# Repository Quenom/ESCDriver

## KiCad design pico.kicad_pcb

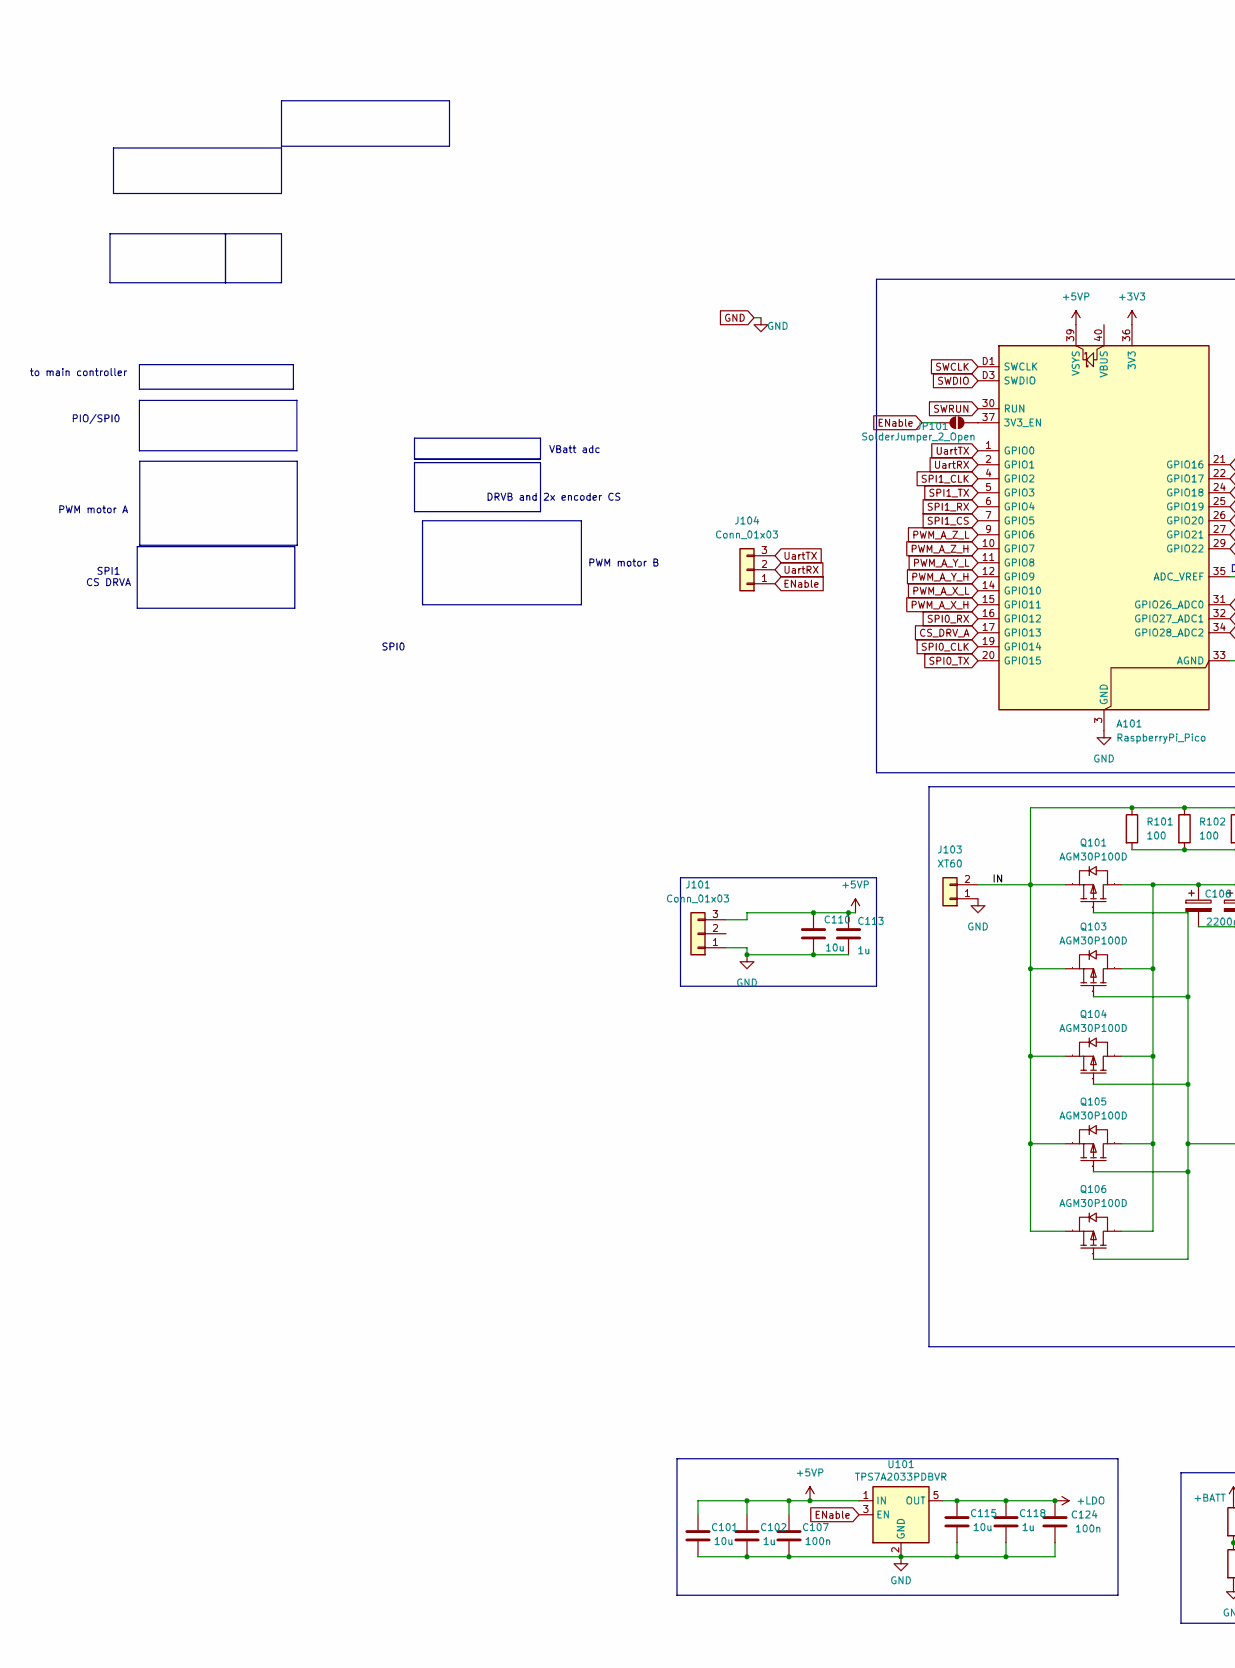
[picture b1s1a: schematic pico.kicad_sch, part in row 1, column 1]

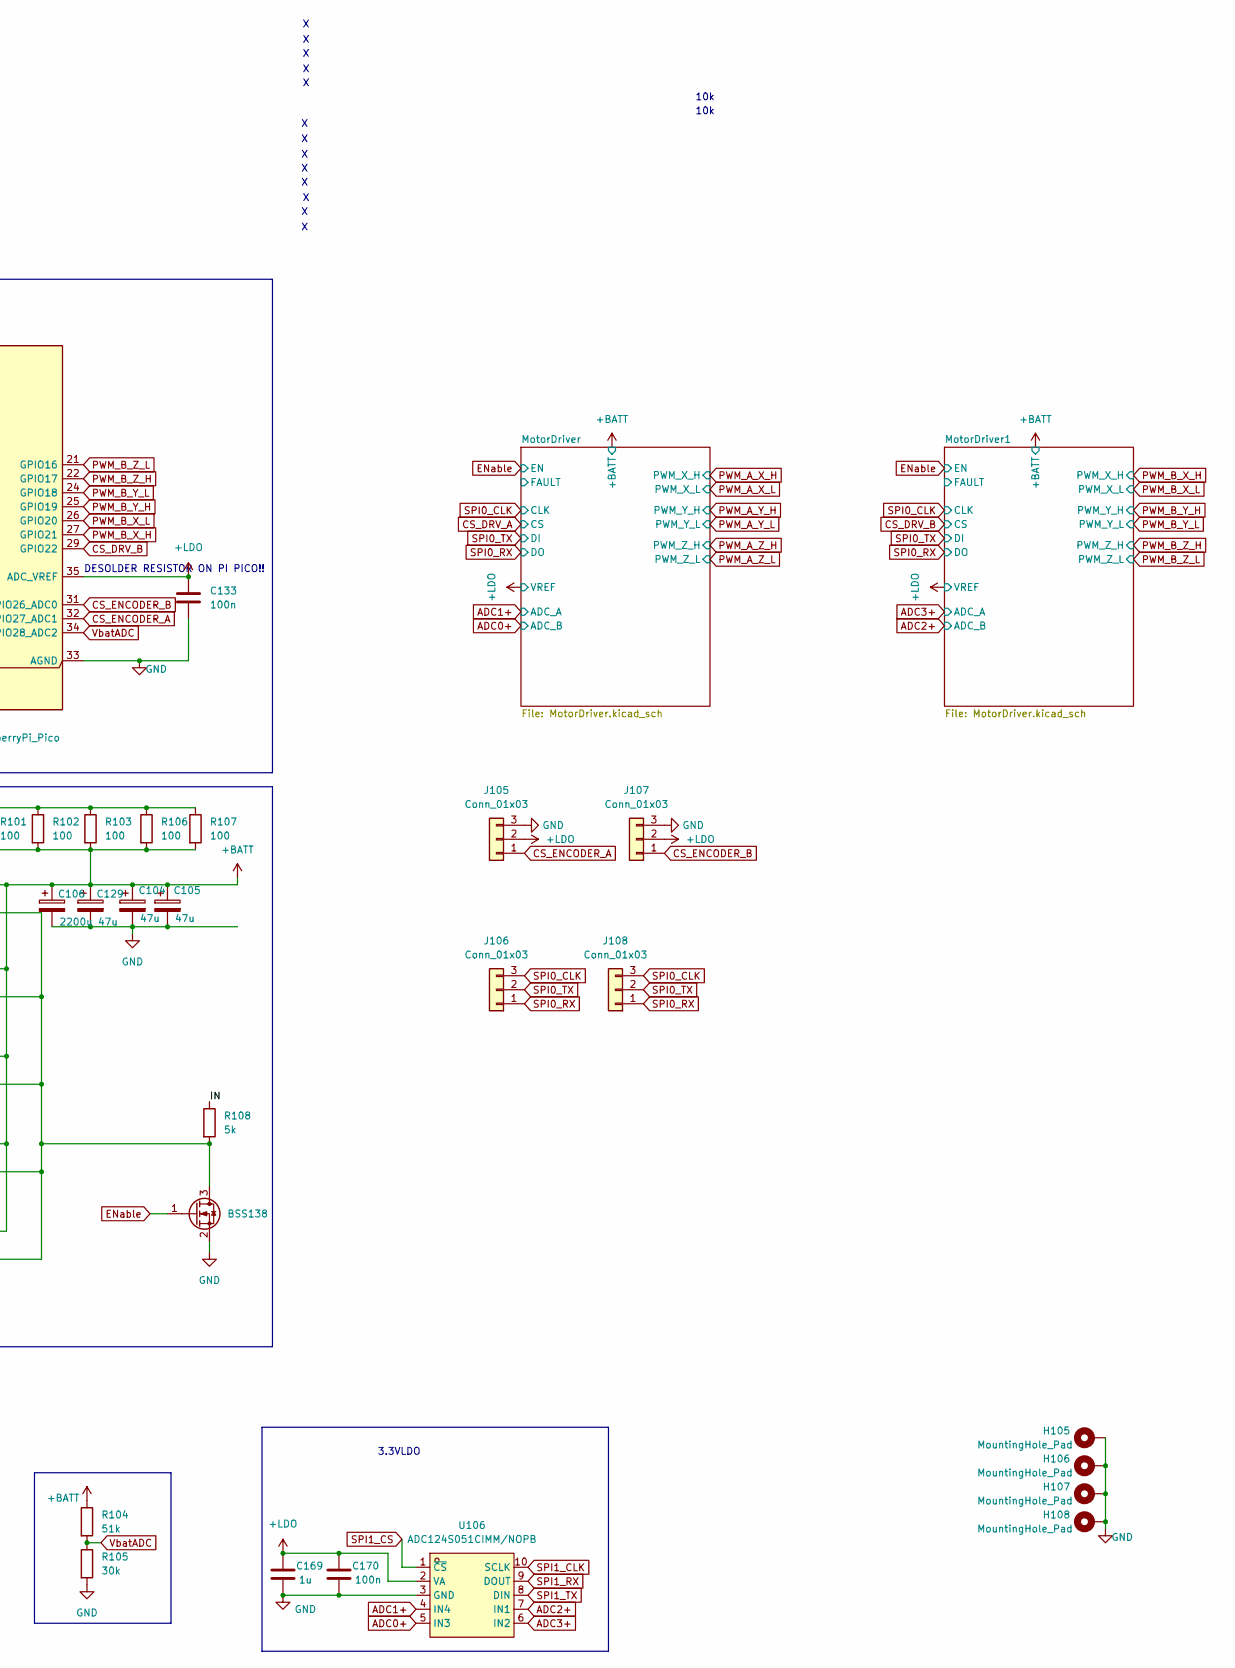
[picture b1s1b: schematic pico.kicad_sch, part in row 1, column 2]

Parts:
A101: RaspberryPi_Pico; RaspberryPi_Pico_SMD_HandSolder
C101, C110, C115: 10u; 1206_Resistor
C102, C113, C118, C169: 1u; 1206_Resistor
C104, C105, C129: 47u; CP_Radial_D6.3mm_P2.50mm
C106: 2200u; CP_Radial_D18.0mm_P7.50mm
C107, C124, C133, C170: 100n; 1206_Resistor
H105, H106, H107, H108: MountingHole_Pad; MountingHole_3.2mm_M3_Pad_Via
J101, J104, J105, J106, J107, J108: Conn_01x03; JST_XH_B3B-XH-A_1x03_P2.50mm_Vertical
J103: XT60; AMASS_XT60PW-M_1x02_P7.20mm_Horizontal
JP101: SolderJumper_2_Open; SolderJumper-2_P1.3mm_Open_RoundedPad1.0x1.5mm
Q101, Q103, Q104, Q105, Q106: AGM30P100D; TO-252-3_L6.6-W6.1-P4.57-LS9.9-BR-CW; Manufacturer Part AGM30P100D; LCSC Part Name 1个P沟道 耐压:30V 电流:128A
Q102: BSS138; SOT-23
R101, R102, R103, R106, R107: 100; 1206_Resistor
R104: 51k; 1206_Resistor
R105: 30k; 1206_Resistor
R108: 5k; 1206_Resistor
U101: TPS7A2033PDBVR; SOT-23-5
U106: ADC124S051CIMM/NOPB; VSSOP-10_L3.0-W3.0-P0.50-LS4.9-BL; Supply Voltage 2.7V~5.25V; LCSC Part C2651323

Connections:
+3V3: A101.36 (3V3)
+5VP: A101.39 (VSYS), C101.1, C102.1, C107.1, C110.1, C113.1, J101.3, U101.1 (IN)
+BATT: C104.1, C105.1, C106.1, C129.1, Q101.2 (D), Q103.2 (D), Q104.2 (D), Q105.2 (D), Q106.2 (D), R101.2, R102.2, R103.2, R104.1, R106.2, R107.2; also elsewhere on the board
+LDO: A101.35 (ADC_VREF), C115.1, C118.1, C124.1, C133.1, C169.1, C170.1, J105.2, J107.2, U101.5 (OUT), U106.2 (VA); also elsewhere on the board
/IN: J103.2, Q101.3 (S), Q103.3 (S), Q104.3 (S), Q105.3 (S), Q106.3 (S), R101.1, R102.1, R103.1, R106.1, R107.1, R108.1
ADC0+: U106.5 (IN3); also elsewhere on the board
ADC1+: U106.4 (IN4); also elsewhere on the board
ADC2+: U106.7 (IN1); also elsewhere on the board
ADC3+: U106.6 (IN2); also elsewhere on the board
CS_DRV_A: A101.17 (GPIO13); also elsewhere on the board
CS_DRV_B: A101.29 (GPIO22); also elsewhere on the board
CS_ENCODER_A: A101.32 (GPIO27_ADC1), J105.1
CS_ENCODER_B: A101.31 (GPIO26_ADC0), J107.1
ENable: J104.1, JP101.1 (A), Q102.1 (G), U101.3 (EN); also elsewhere on the board
GND: A101.3 (GND), A101.8 (GND), A101.13 (GND), A101.18 (GND), A101.23 (GND), A101.28 (GND), A101.33 (AGND), A101.38 (GND), A101.D2 (GND), C101.2, C102.2, C104.2, C105.2, C106.2, C107.2, C110.2, C113.2, C115.2, C118.2, C124.2, C129.2, C133.2, C169.2, C170.2, H105.1, H106.1, H107.1, H108.1, J101.1, J103.1, J105.3, J107.3, Q102.2 (S), R105.2, U101.2 (GND), U106.3 (GND); also elsewhere on the board
unnamed: A101.37 (3V3_EN), JP101.2 (B)
unnamed: Q101.1 (G), Q102.3 (D), Q103.1 (G), Q104.1 (G), Q105.1 (G), Q106.1 (G), R108.2
PWM_A_X_H: A101.15 (GPIO11); also elsewhere on the board
PWM_A_X_L: A101.14 (GPIO10); also elsewhere on the board
PWM_A_Y_H: A101.12 (GPIO9); also elsewhere on the board
PWM_A_Y_L: A101.11 (GPIO8); also elsewhere on the board
PWM_A_Z_H: A101.10 (GPIO7); also elsewhere on the board
PWM_A_Z_L: A101.9 (GPIO6); also elsewhere on the board
PWM_B_X_H: A101.27 (GPIO21); also elsewhere on the board
PWM_B_X_L: A101.26 (GPIO20); also elsewhere on the board
PWM_B_Y_H: A101.25 (GPIO19); also elsewhere on the board
PWM_B_Y_L: A101.24 (GPIO18); also elsewhere on the board
PWM_B_Z_H: A101.22 (GPIO17); also elsewhere on the board
PWM_B_Z_L: A101.21 (GPIO16); also elsewhere on the board
SPI0_CLK: A101.19 (GPIO14), J106.3, J108.3; also elsewhere on the board
SPI0_RX: A101.16 (GPIO12), J106.1, J108.1; also elsewhere on the board
SPI0_TX: A101.20 (GPIO15), J106.2, J108.2; also elsewhere on the board
SPI1_CLK: A101.4 (GPIO2), U106.10 (SCLK)
SPI1_CS: A101.7 (GPIO5), U106.1 (~CS)
SPI1_RX: A101.6 (GPIO4), U106.9 (DOUT)
SPI1_TX: A101.5 (GPIO3), U106.8 (DIN)
SWCLK: A101.D1 (SWCLK)
SWDIO: A101.D3 (SWDIO)
SWRUN: A101.30 (RUN)
UartRX: A101.2 (GPIO1), J104.2
UartTX: A101.1 (GPIO0), J104.3
VbatADC: A101.34 (GPIO28_ADC2), R104.2, R105.1

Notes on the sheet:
3.3VLDO
PIO/SPI0
DRVB and 2x encoder CS
SPI0
DESOLDER RESISTOR ON PI PICO!!
PWM motor A
VBatt adc
PWM motor B
SPI1 CS DRVA
10k
to main controller

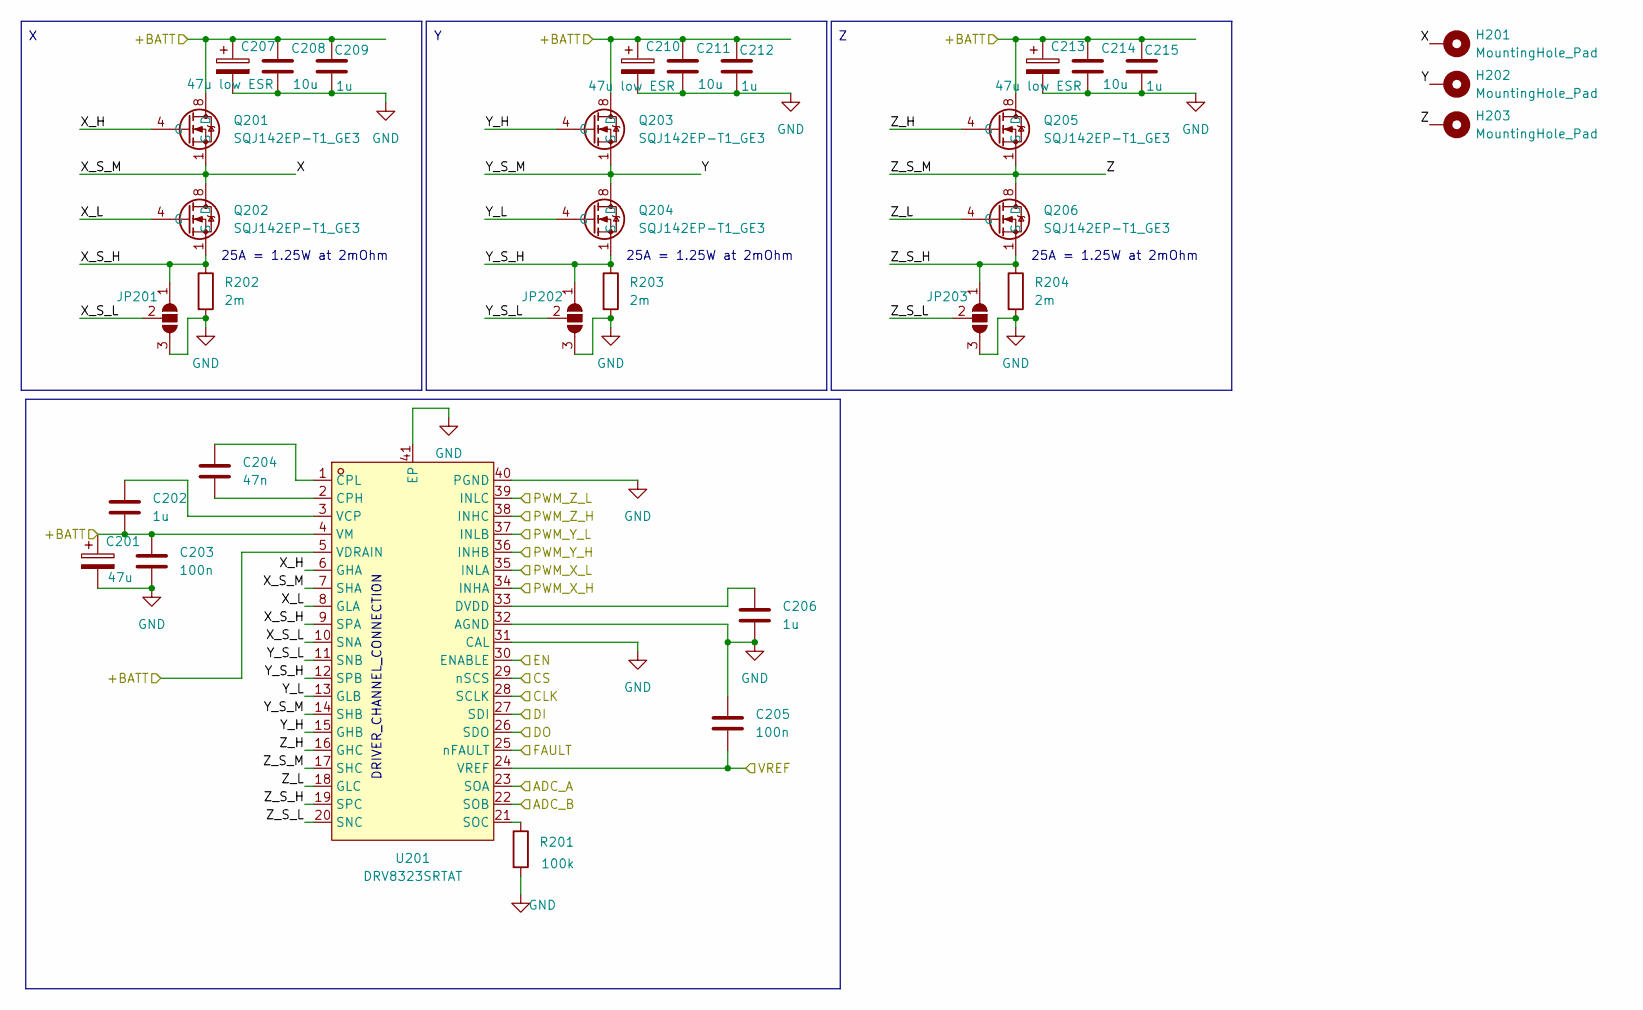
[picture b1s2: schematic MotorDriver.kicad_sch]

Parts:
C201: 47u; CP_Radial_D6.3mm_P2.50mm
C202, C206, C209, C212, C215: 1u; 1206_Resistor
C203, C205: 100n; 1206_Resistor
C204: 47n; 1206_Resistor
C207, C210, C213: 47u low ESR; CP_Radial_D6.3mm_P2.50mm
C208, C211, C214: 10u; 1206_Resistor
H201, H202, H203: MountingHole_Pad; SolderWire-2sqmm_1x01_D2mm_OD3.9mm
JP201, JP202, JP203: SolderJumper_3_Open; SolderJumper-3_P1.3mm_Open_RoundedPad1.0x1.5mm_NumberLabels
Q201, Q202, Q203, Q204, Q205, Q206: SQJ142EP-T1_GE3; POWERPAK-SO-8_L5.9-W4.9-P1.27-BL; LCSC Part C5758799
R201: 100k; 1206_Resistor
R202, R203, R204: 2m; R_2512_6332Metric_Pad1.40x3.35mm_HandSolder
U201: DRV8323SRTAT; WQFN-40_L6.0-W6.0-P0.50-TL-EP4.5; Supply Voltage 6V~60V; LCSC Part C2150452

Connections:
+BATT: C201.1, C202.2, C203.1, C207.1, C208.1, C209.1, C210.1, C211.1, C212.1, C213.1, C214.1, C215.1, Q201.8 (D), Q203.8 (D), Q205.8 (D), U201.4 (VM), U201.5 (VDRAIN); also elsewhere on the board
+LDO: C205.2, U201.24 (VREF); also elsewhere on the board
/MotorDriver/FAULT: U201.25 (nFAULT)
/MotorDriver/X: H201.1, Q201.1 (S), Q202.8 (D), U201.7 (SHA)
/MotorDriver/X_H: Q201.4 (G), U201.6 (GHA)
/MotorDriver/X_L: Q202.4 (G), U201.8 (GLA)
/MotorDriver/X_S_H: JP201.1 (A), Q202.1 (S), R202.1, U201.9 (SPA)
/MotorDriver/X_S_L: JP201.2 (C), U201.10 (SNA)
/MotorDriver/Y: H202.1, Q203.1 (S), Q204.8 (D), U201.14 (SHB)
/MotorDriver/Y_H: Q203.4 (G), U201.15 (GHB)
/MotorDriver/Y_L: Q204.4 (G), U201.13 (GLB)
/MotorDriver/Y_S_H: JP202.1 (A), Q204.1 (S), R203.1, U201.12 (SPB)
/MotorDriver/Y_S_L: JP202.2 (C), U201.11 (SNB)
/MotorDriver/Z: H203.1, Q205.1 (S), Q206.8 (D), U201.17 (SHC)
/MotorDriver/Z_H: Q205.4 (G), U201.16 (GHC)
/MotorDriver/Z_L: Q206.4 (G), U201.18 (GLC)
/MotorDriver/Z_S_H: JP203.1 (A), Q206.1 (S), R204.1, U201.19 (SPC)
/MotorDriver/Z_S_L: JP203.2 (C), U201.20 (SNC)
ADC0+: U201.22 (SOB); also elsewhere on the board
ADC1+: U201.23 (SOA); also elsewhere on the board
CS_DRV_A: U201.29 (nSCS); also elsewhere on the board
ENable: U201.30 (ENABLE); also elsewhere on the board
GND: C201.2, C203.2, C205.1, C206.2, C207.2, C208.2, C209.2, C210.2, C211.2, C212.2, C213.2, C214.2, C215.2, JP201.3 (B), JP202.3 (B), JP203.3 (B), R201.2, R202.2, R203.2, R204.2, U201.31 (CAL), U201.32 (AGND), U201.40 (PGND), U201.41 (EP); also elsewhere on the board
unnamed: C204.2, U201.2 (CPH)
unnamed: C204.1, U201.1 (CPL)
unnamed: C206.1, U201.33 (DVDD)
unnamed: R201.1, U201.21 (SOC)
unnamed: C202.1, U201.3 (VCP)
PWM_A_X_H: U201.34 (INHA); also elsewhere on the board
PWM_A_X_L: U201.35 (INLA); also elsewhere on the board
PWM_A_Y_H: U201.36 (INHB); also elsewhere on the board
PWM_A_Y_L: U201.37 (INLB); also elsewhere on the board
PWM_A_Z_H: U201.38 (INHC); also elsewhere on the board
PWM_A_Z_L: U201.39 (INLC); also elsewhere on the board
SPI0_CLK: U201.28 (SCLK); also elsewhere on the board
SPI0_RX: U201.26 (SDO); also elsewhere on the board
SPI0_TX: U201.27 (SDI); also elsewhere on the board

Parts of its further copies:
C301: 47u; CP_Radial_D6.3mm_P2.50mm
C302, C307, C311, C312, C315: 1u; 1206_Resistor
C303, C310: 100n; 1206_Resistor
C304: 47n; 1206_Resistor
C305, C308, C313: 47u low ESR; CP_Radial_D6.3mm_P2.50mm
C306, C309, C314: 10u; 1206_Resistor
H301, H302, H303: MountingHole_Pad; SolderWire-2sqmm_1x01_D2mm_OD3.9mm
JP301, JP302, JP303: SolderJumper_3_Open; SolderJumper-3_P1.3mm_Open_RoundedPad1.0x1.5mm_NumberLabels
Q301, Q302, Q303, Q304, Q305, Q306: SQJ142EP-T1_GE3; POWERPAK-SO-8_L5.9-W4.9-P1.27-BL; LCSC Part C5758799
R301, R303, R304: 2m; R_2512_6332Metric_Pad1.40x3.35mm_HandSolder
R302: 100k; 1206_Resistor
U301: DRV8323SRTAT; WQFN-40_L6.0-W6.0-P0.50-TL-EP4.5; Supply Voltage 6V~60V; LCSC Part C2150452

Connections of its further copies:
+BATT: C301.1, C302.2, C303.1, C305.1, C306.1, C307.1, C308.1, C309.1, C311.1, C313.1, C314.1, C315.1, Q301.8 (D), Q303.8 (D), Q305.8 (D), U301.4 (VM), U301.5 (VDRAIN); also elsewhere on the board
+LDO: C310.2, U301.24 (VREF); also elsewhere on the board
/MotorDriver1/FAULT: U301.25 (nFAULT)
/MotorDriver1/X: H301.1, Q301.1 (S), Q302.8 (D), U301.7 (SHA)
/MotorDriver1/X_H: Q301.4 (G), U301.6 (GHA)
/MotorDriver1/X_L: Q302.4 (G), U301.8 (GLA)
/MotorDriver1/X_S_H: JP301.1 (A), Q302.1 (S), R301.1, U301.9 (SPA)
/MotorDriver1/X_S_L: JP301.2 (C), U301.10 (SNA)
/MotorDriver1/Y: H302.1, Q303.1 (S), Q304.8 (D), U301.14 (SHB)
/MotorDriver1/Y_H: Q303.4 (G), U301.15 (GHB)
/MotorDriver1/Y_L: Q304.4 (G), U301.13 (GLB)
/MotorDriver1/Y_S_H: JP302.1 (A), Q304.1 (S), R303.1, U301.12 (SPB)
/MotorDriver1/Y_S_L: JP302.2 (C), U301.11 (SNB)
/MotorDriver1/Z: H303.1, Q305.1 (S), Q306.8 (D), U301.17 (SHC)
/MotorDriver1/Z_H: Q305.4 (G), U301.16 (GHC)
/MotorDriver1/Z_L: Q306.4 (G), U301.18 (GLC)
/MotorDriver1/Z_S_H: JP303.1 (A), Q306.1 (S), R304.1, U301.19 (SPC)
/MotorDriver1/Z_S_L: JP303.2 (C), U301.20 (SNC)
ADC2+: U301.22 (SOB); also elsewhere on the board
ADC3+: U301.23 (SOA); also elsewhere on the board
CS_DRV_B: U301.29 (nSCS); also elsewhere on the board
ENable: U301.30 (ENABLE); also elsewhere on the board
GND: C301.2, C303.2, C305.2, C306.2, C307.2, C308.2, C309.2, C310.1, C311.2, C312.2, C313.2, C314.2, C315.2, JP301.3 (B), JP302.3 (B), JP303.3 (B), R301.2, R302.2, R303.2, R304.2, U301.31 (CAL), U301.32 (AGND), U301.40 (PGND), U301.41 (EP); also elsewhere on the board
unnamed: C304.2, U301.2 (CPH)
unnamed: C304.1, U301.1 (CPL)
unnamed: C312.1, U301.33 (DVDD)
unnamed: R302.1, U301.21 (SOC)
unnamed: C302.1, U301.3 (VCP)
PWM_B_X_H: U301.34 (INHA); also elsewhere on the board
PWM_B_X_L: U301.35 (INLA); also elsewhere on the board
PWM_B_Y_H: U301.36 (INHB); also elsewhere on the board
PWM_B_Y_L: U301.37 (INLB); also elsewhere on the board
PWM_B_Z_H: U301.38 (INHC); also elsewhere on the board
PWM_B_Z_L: U301.39 (INLC); also elsewhere on the board
SPI0_CLK: U301.28 (SCLK); also elsewhere on the board
SPI0_RX: U301.26 (SDO); also elsewhere on the board
SPI0_TX: U301.27 (SDI); also elsewhere on the board

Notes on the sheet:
25A = 1.25W at 2mOhm
DRIVER_CHANNEL_CONNECTION

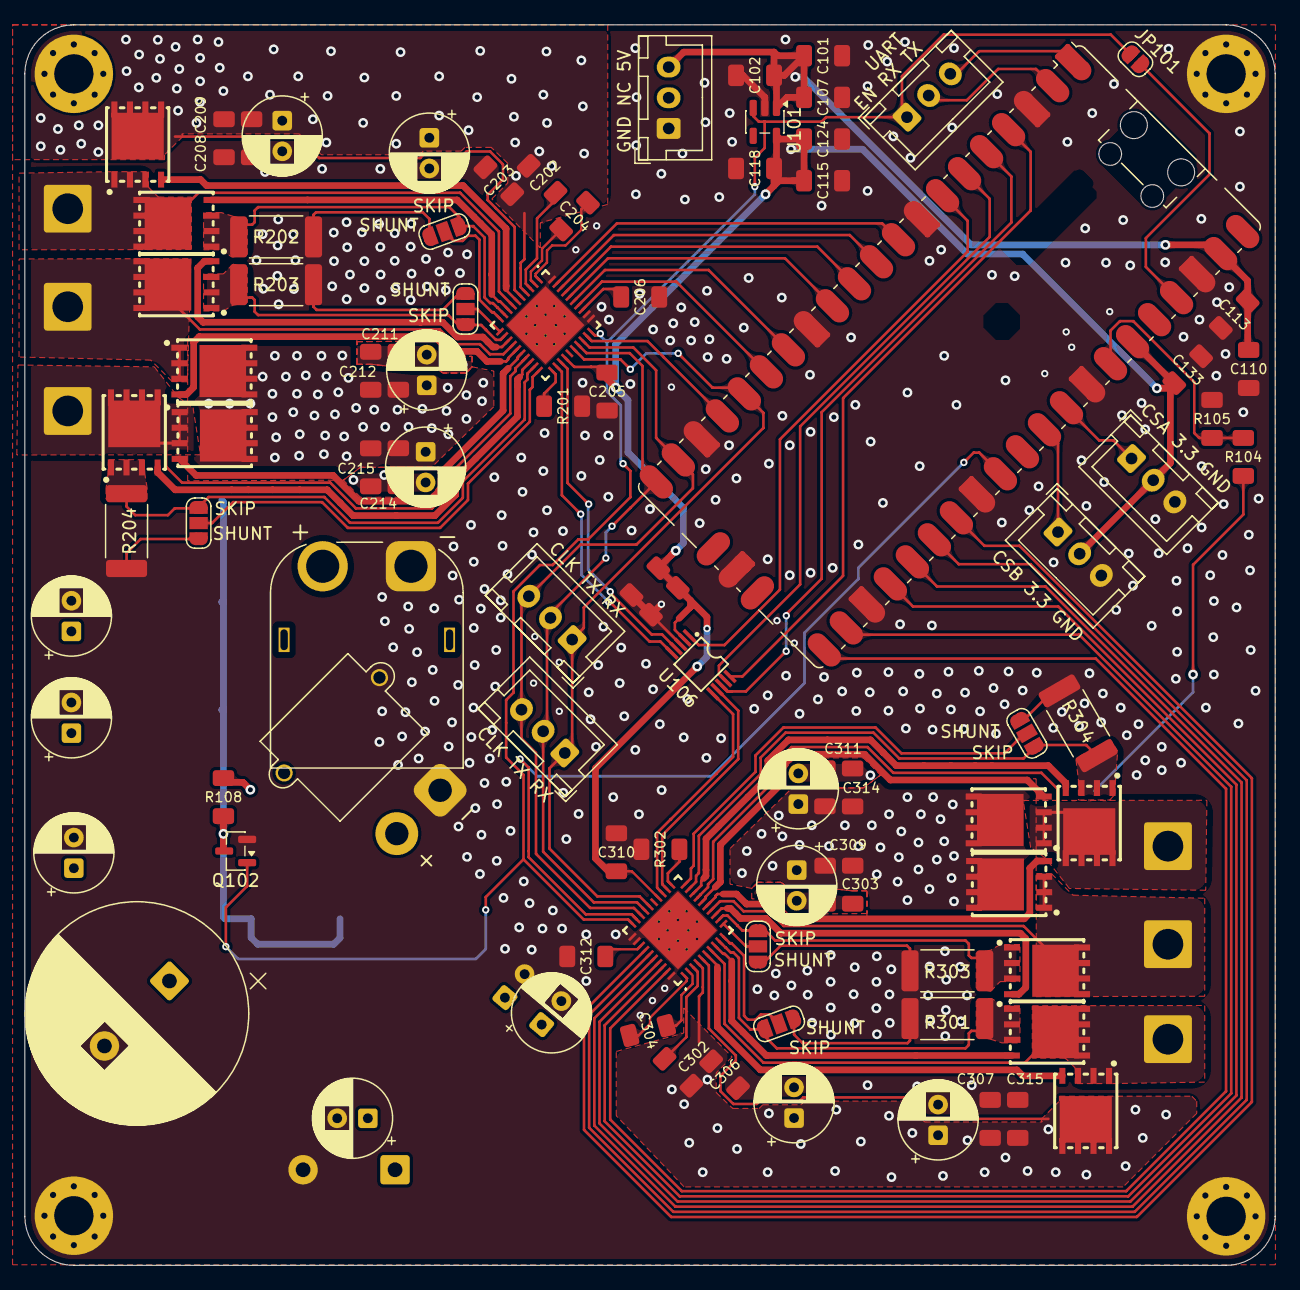
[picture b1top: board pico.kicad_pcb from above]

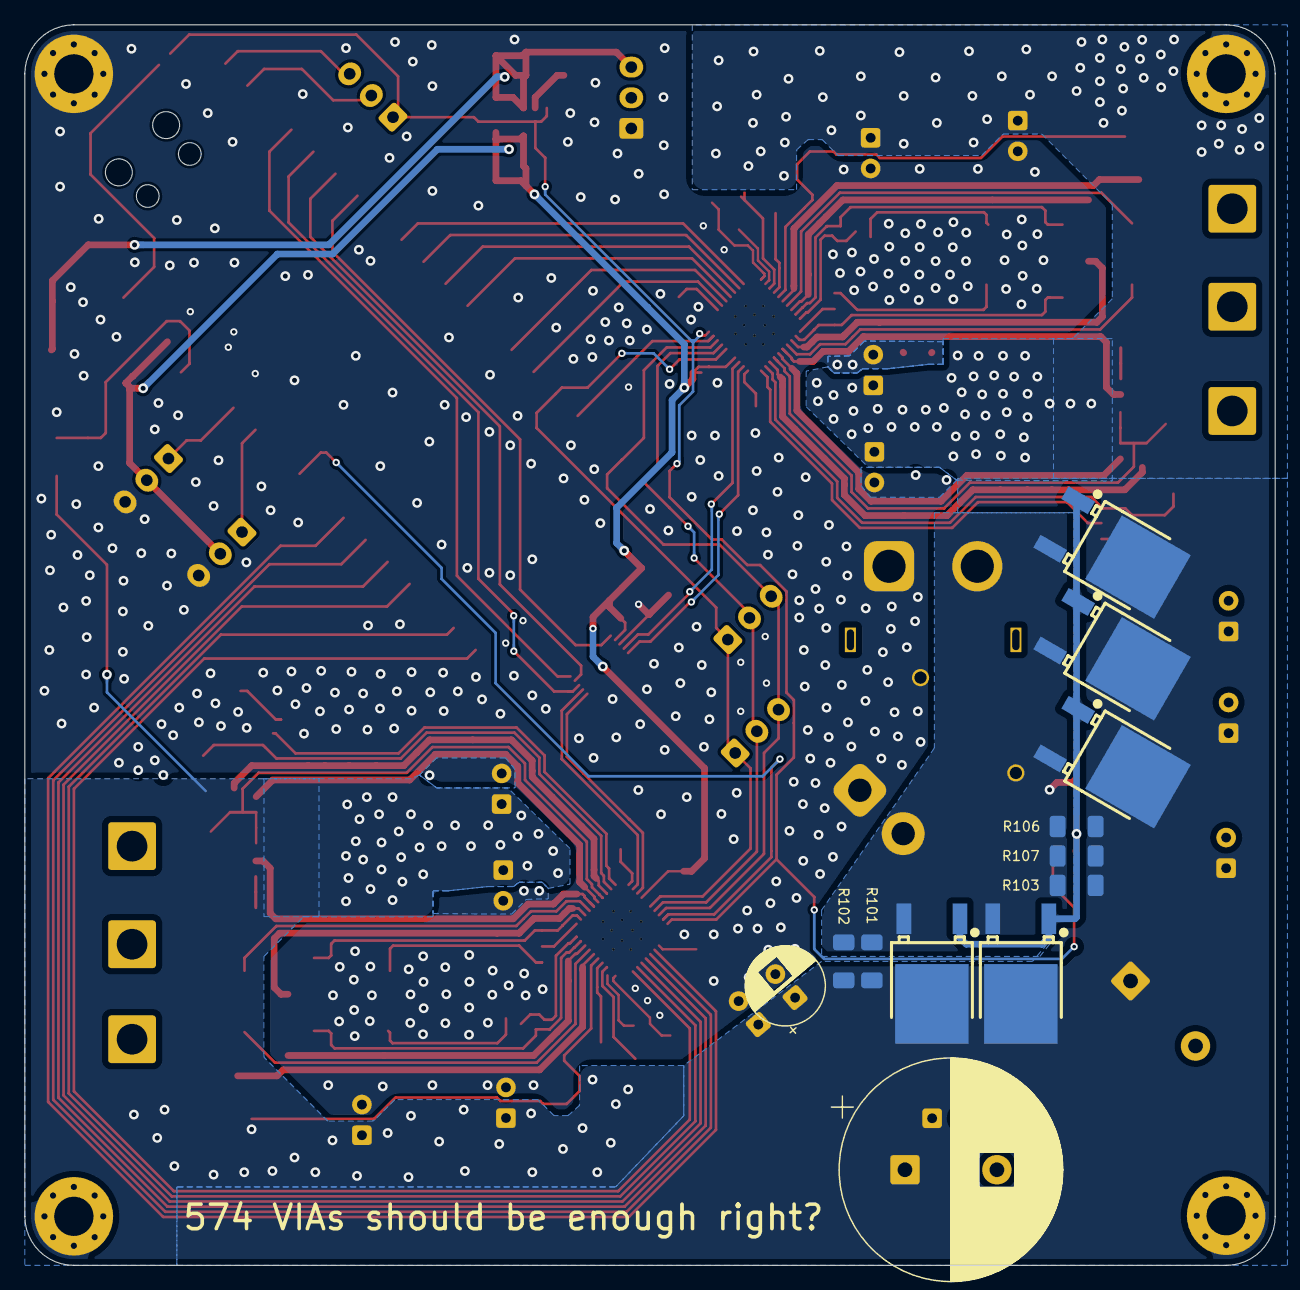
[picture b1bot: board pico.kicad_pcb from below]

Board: 2 copper layers, 102.0 x 101.2 mm, 112 parts (12 on the bottom side), 78 nets.

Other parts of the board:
C104#2, C104#3, C129#2: 47u; CP_Radial_D6.3mm_P2.50mm
C106#2: 2200u; CP_Radial_D18.0mm_P7.50mm

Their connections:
+BATT: C104#2.1, C104#3.1, C106#2.1, C129#2.1; also elsewhere on the board
GND: C104#2.2, C104#3.2, C106#2.2, C129#2.2; also elsewhere on the board

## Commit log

2026-03-31 seprate motors
2026-03-31 stuff
2026-03-31 finished driverA
2026-03-31 hope it works(git)
2026-04-01 progress on pcb todo:encoders
2026-04-01 added m3 mounting holes
2026-04-01 ewdwad
2026-04-01 wdawdawd
2026-04-06 why every commit needs a message
2026-04-07 Good progress
2026-04-09 done?
2026-04-10 wrong connector
2026-04-10 via stiching trzeba
2026-04-13 m, mn,
2026-04-14 final
